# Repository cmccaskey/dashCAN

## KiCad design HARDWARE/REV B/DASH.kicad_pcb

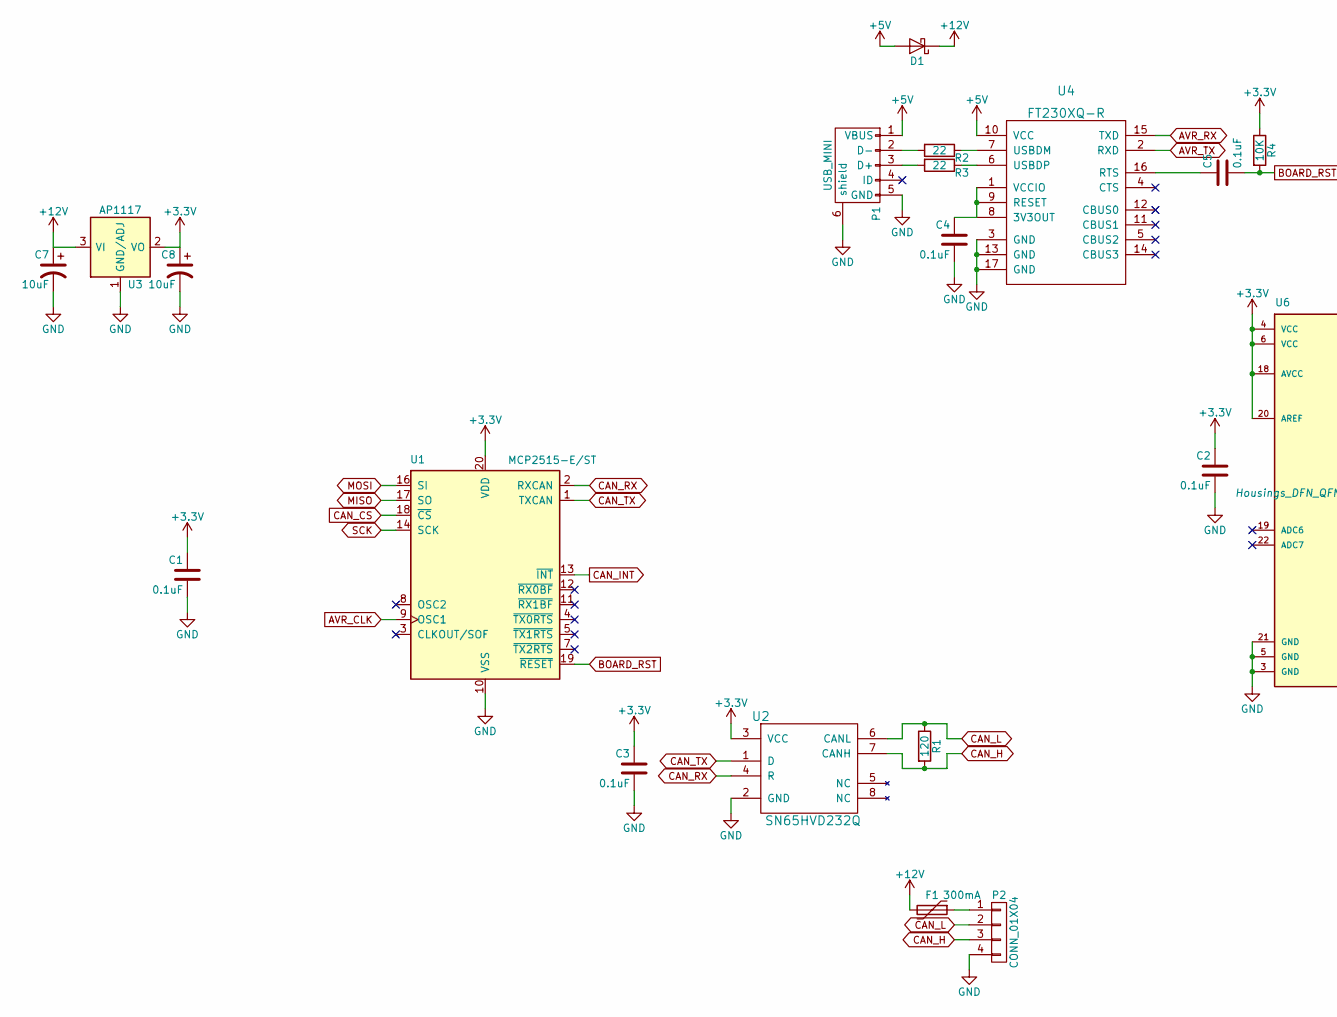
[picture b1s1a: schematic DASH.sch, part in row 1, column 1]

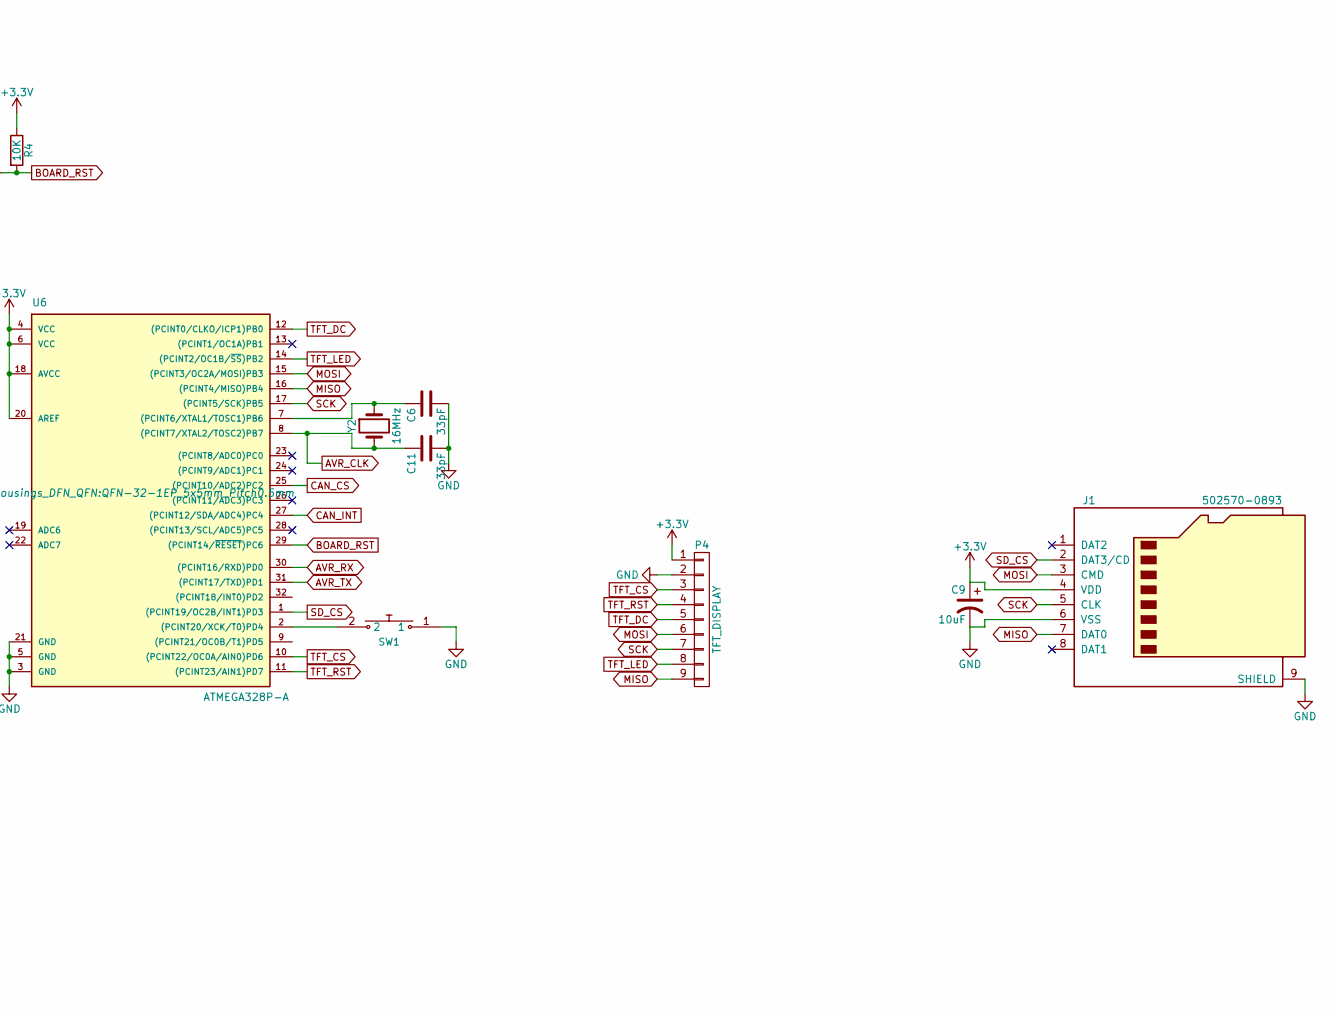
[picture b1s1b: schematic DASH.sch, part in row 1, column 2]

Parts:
C1, C2, C3, C4, C5: 0.1uF; C_0603
C6, C11: 33pF; C_0603
C7, C8, C9: 10uF; Tantalum_Case-A_EIA-3216-18_Reflow
D1: D_Schottky; SOD-323
F1: 300mA; R_1206
J1: 502570-0893; MOLEX_502570-0893
P1: USB_MINI; UX60-MB-5ST
P2: CONN_01X04; JST_PH_S4B-PH-K_04x2.00mm_Angled
P4: TFT_DISPLAY; Pin_Header_Straight_1x09
R1: 120; R_0603
R2, R3: 22; R_0603
R4: 10K; R_0603
SW1: Push_SW; SW_Tactile_SPST_Angled
U1: MCP2515-E/ST; TSSOP-20_4.4x6.5mm_Pitch0.65mm
U2: SN65HVD232Q; SOIC-8_3.9x4.9mm_Pitch1.27mm
U3: AP1117; SOT-223
U4: FT230XQ-R; QFN-16-1EP_4x4mm_Pitch0.65mm
U6: ATMEGA328P-A; QFN-32-1EP_5x5mm_Pitch0.5mm
Y2: 16MHz; ABM3

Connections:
+3V3: C1.1, C2.1, C3.1, C8.1, C9.1, J1.4 (VDD), P4.1, R4.1, U1.20 (VDD), U2.3 (VCC), U3.2 (VO), U3.4 (VO), U6.4 (VCC), U6.6 (VCC), U6.18 (AVCC), U6.20 (AREF)
+5V: D1.2 (A), P1.1 (VBUS), U4.10 (VCC)
+12V: C7.1, D1.1 (K), F1.2, U3.3 (VI)
AVR_CLK: C11.1, U1.9 (OSC1), U6.8 ((PCINT7/XTAL2/TOSC2)PB7), Y2.2
AVR_RX: U4.15 (TXD), U6.30 ((PCINT16/RXD)PD0)
AVR_TX: U4.2 (RXD), U6.31 ((PCINT17/TXD)PD1)
BOARD_RST: C5.2, R4.2, U1.19 (~RESET), U6.29 ((PCINT14/~RESET~)PC6)
CAN_CS: U1.18 (~CS), U6.25 ((PCINT10/ADC2)PC2)
CAN_H: P2.3, R1.2, U2.7 (CANH)
CAN_INT: U1.13 (~INT), U6.27 ((PCINT12/SDA/ADC4)PC4)
CAN_L: P2.2, R1.1, U2.6 (CANL)
CAN_RX: U1.2 (RXCAN), U2.4 (R)
CAN_TX: U1.1 (TXCAN), U2.1 (D)
GND: C1.2, C2.2, C3.2, C4.2, C6.2, C7.2, C8.2, C9.2, C11.2, J1.6 (VSS), J1.9 (SHIELD), P1.5 (GND), P1.6 (shield), P2.4, P4.2, SW1.1, U1.10 (VSS), U2.2 (GND), U3.1 (GND/ADJ), U4.3 (GND), U4.13 (GND), U4.17 (GND), U6.3 (GND), U6.5 (GND), U6.21 (GND); also elsewhere on the board
MISO: J1.7 (DAT0), P4.9, U1.17 (SO), U6.16 ((PCINT4/MISO)PB4)
MOSI: J1.3 (CMD), P4.6, U1.16 (SI), U6.15 ((PCINT3/OC2A/MOSI)PB3)
unnamed: C4.1, U4.1 (VCCIO), U4.8 (3V3OUT), U4.9 (RESET)
unnamed: C5.1, U4.16 (RTS)
unnamed: C6.1, U6.7 ((PCINT6/XTAL1/TOSC1)PB6), Y2.1
unnamed: F1.1, P2.1
unnamed: P1.2 (D-), R2.2
unnamed: P1.3 (D+), R3.2
unnamed: R2.1, U4.7 (USBDM)
unnamed: R3.1, U4.6 (USBDP)
unnamed: SW1.2, U6.2 ((PCINT20/XCK/T0)PD4)
SCK: J1.5 (CLK), P4.7, U1.14 (SCK), U6.17 ((PCINT5/SCK)PB5)
SD_CS: J1.2 (DAT3/CD), U6.1 ((PCINT19/OC2B/INT1)PD3)
TFT_CS: P4.3, U6.10 ((PCINT22/OC0A/AIN0)PD6)
TFT_DC: P4.5, U6.12 ((PCINT0/CLKO/ICP1)PB0)
TFT_LED: P4.8, U6.14 ((PCINT2/OC1B/~SS~)PB2)
TFT_RST: P4.4, U6.11 ((PCINT23/AIN1)PD7)

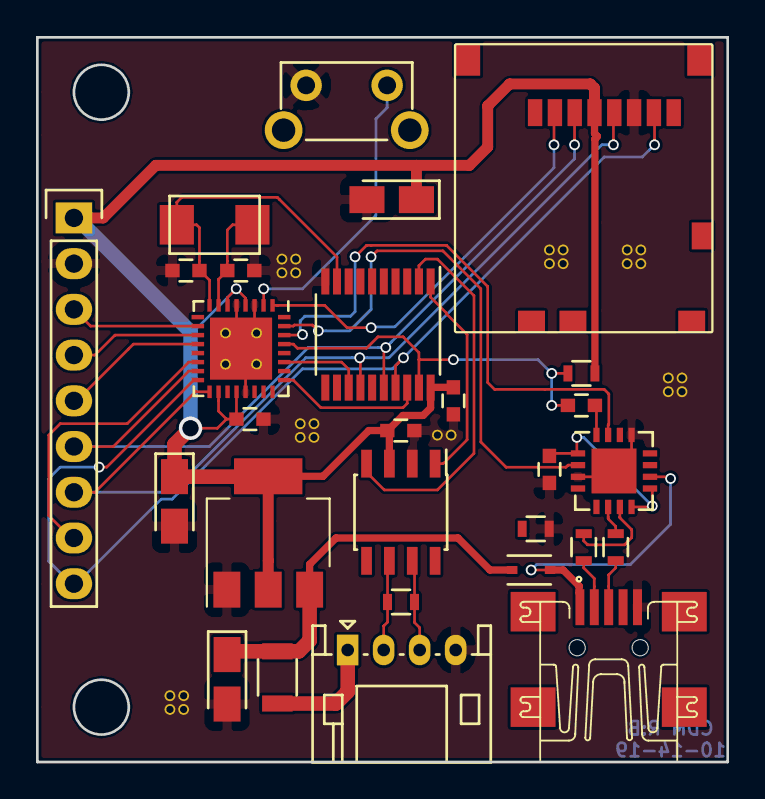
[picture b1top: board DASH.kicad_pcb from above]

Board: 2 copper layers, 38.4 x 40.3 mm, 28 parts (0 on the bottom side), 31 nets.

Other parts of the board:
R7: 100K; R_0603

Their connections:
GND: R7.2; also elsewhere on the board

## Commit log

2019-09-15 init
2019-09-15 code
2019-10-20 images
